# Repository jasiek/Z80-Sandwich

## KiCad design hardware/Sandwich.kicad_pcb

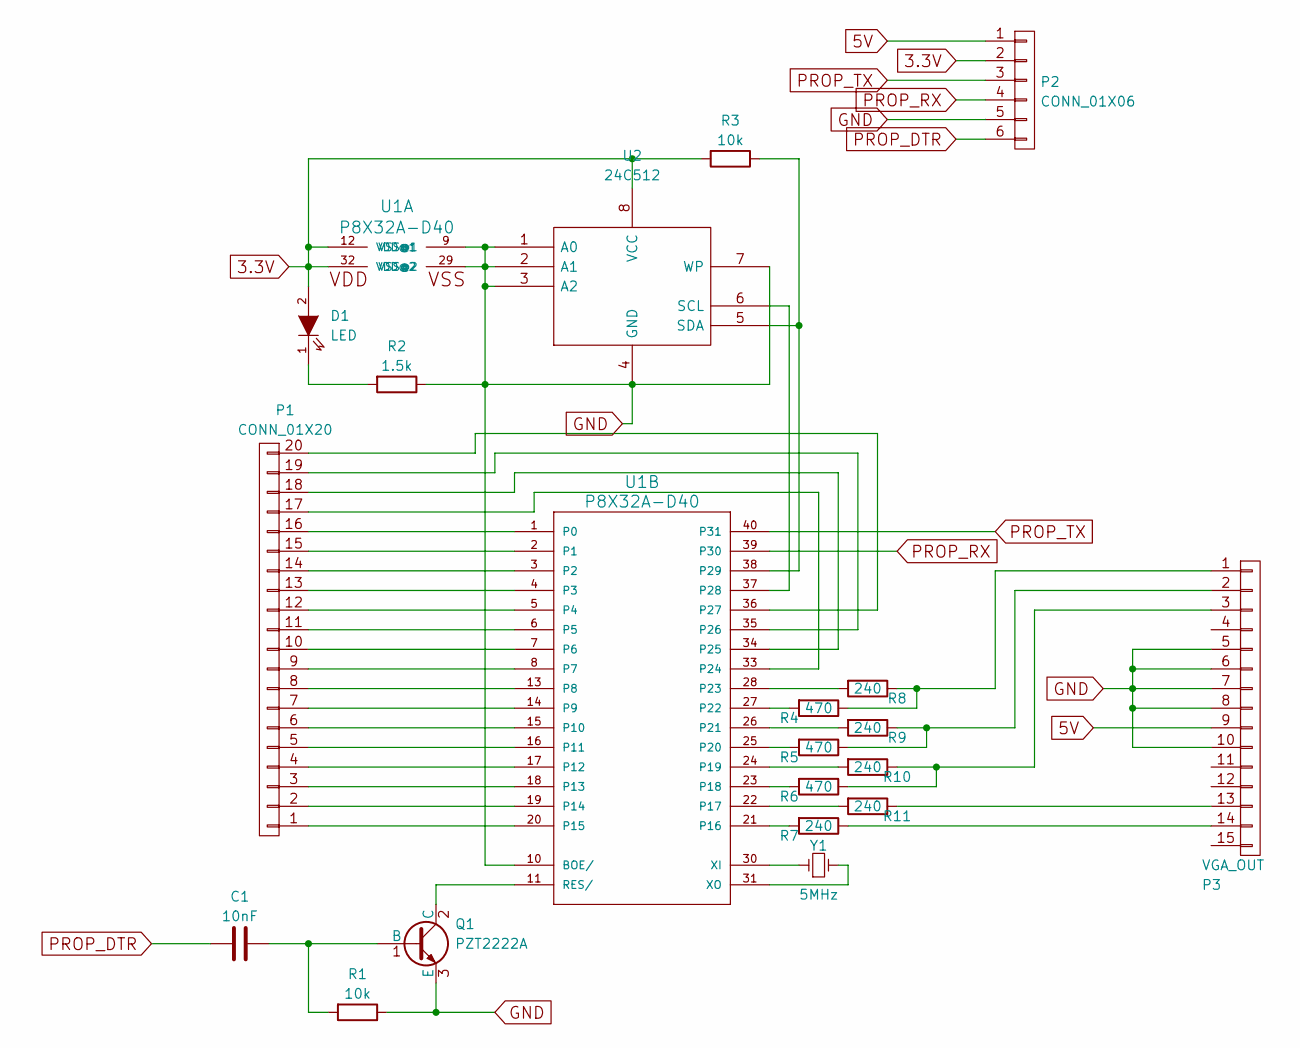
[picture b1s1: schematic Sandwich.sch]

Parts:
C1: 10nF; C_Disc_D3_P2.5
D1: LED; LED-5MM
P1: CONN_01X20; Pin_Header_Straight_1x20
P2: CONN_01X06; Pin_Header_Straight_1x06
P3: VGA_OUT; conn_SPC15430
Q1: PZT2222A; SOT-223
R1, R3: 10k; Resistor_Horizontal_RM10mm
R2: 1.5k; Resistor_Horizontal_RM10mm
R4, R5, R6: 470; Resistor_Horizontal_RM10mm
R7, R8, R9, R10, R11: 240; Resistor_Horizontal_RM10mm
U1: P8X32A-D40; DIP-40_W15.24mm_LongPads
U2: 24C512; DIP-8_W7.62mm_LongPads
Y1: 5MHz; Crystal_HC49-U_Vertical

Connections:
3.3V: D1.2 (A), P2.2, R3.2, U1.12 (VDD@1), U1.32 (VDD@2), U2.8 (VCC); also elsewhere on the board
5V: P2.1, P3.9
GND: P2.5, P3.5, P3.6, P3.7, P3.8, P3.10, Q1.3 (E), R1.1, R2.1, U1.9 (VSS@1), U1.10 (BOE/), U1.29 (VSS@2), U2.1 (A0), U2.2 (A1), U2.3 (A2), U2.4 (GND), U2.7 (WP); also elsewhere on the board
unnamed: C1.1, Q1.1 (B), R1.2
unnamed: D1.1 (K), R2.2
unnamed: P1.1, U1.20 (P15)
unnamed: P1.2, U1.19 (P14)
unnamed: P1.3, U1.18 (P13)
unnamed: P1.4, U1.17 (P12)
unnamed: P1.5, U1.16 (P11)
unnamed: P1.6, U1.15 (P10)
unnamed: P1.7, U1.14 (P9)
unnamed: P1.8, U1.13 (P8)
unnamed: P1.9, U1.8 (P7)
unnamed: P1.10, U1.7 (P6)
unnamed: P1.11, U1.6 (P5)
unnamed: P1.12, U1.5 (P4)
unnamed: P1.13, U1.4 (P3)
unnamed: P1.14, U1.3 (P2)
unnamed: P1.15, U1.2 (P1)
unnamed: P1.16, U1.1 (P0)
unnamed: P1.17, U1.33 (P24)
unnamed: P1.18, U1.34 (P25)
unnamed: P1.19, U1.35 (P26)
unnamed: P1.20, U1.36 (P27)
unnamed: P3.1, R4.1, R8.1
unnamed: P3.2, R5.1, R9.1
unnamed: P3.3, R6.1, R10.1
unnamed: P3.13, R11.1
unnamed: P3.14, R7.1
unnamed: Q1.2 (C), U1.11 (RES/)
unnamed: R3.1, U1.38 (P29), U2.5 (SDA)
unnamed: R4.2, U1.27 (P22)
unnamed: R5.2, U1.25 (P20)
unnamed: R6.2, U1.23 (P18)
unnamed: R7.2, U1.21 (P16)
unnamed: R8.2, U1.28 (P23)
unnamed: R9.2, U1.26 (P21)
unnamed: R10.2, U1.24 (P19)
unnamed: R11.2, U1.22 (P17)
unnamed: U1.30 (XI), Y1.1
unnamed: U1.31 (XO), Y1.2
unnamed: U1.37 (P28), U2.6 (SCL)
PROP_DTR: C1.2, P2.6
PROP_RX: P2.4, U1.39 (P30)
PROP_TX: P2.3, U1.40 (P31)

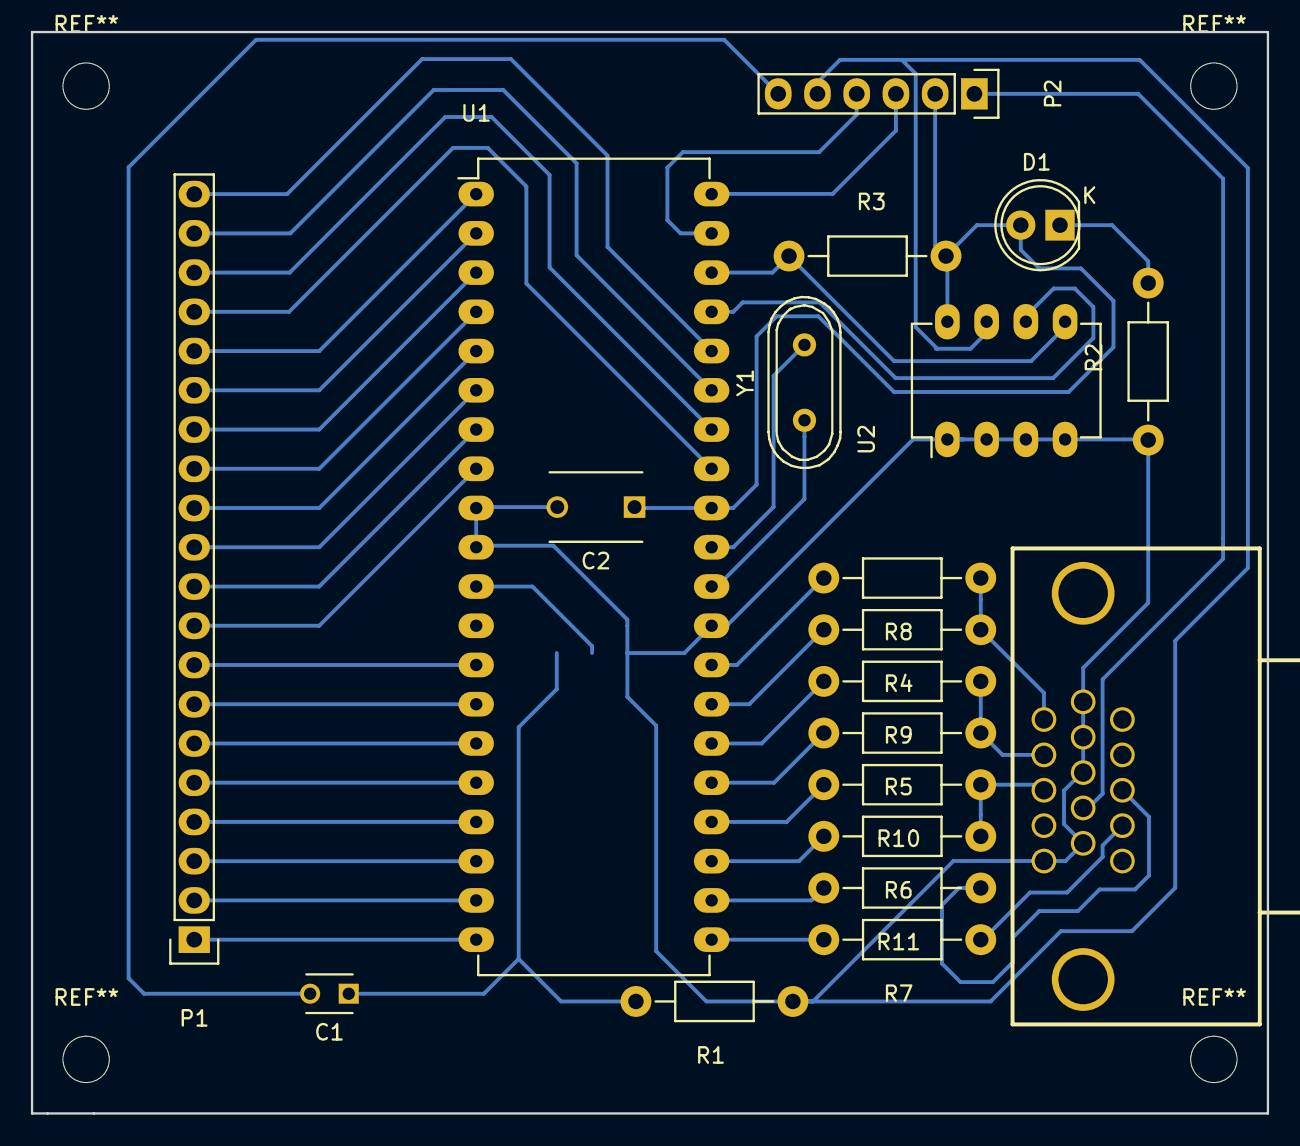
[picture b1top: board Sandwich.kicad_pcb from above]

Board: 2 copper layers, 80.0 x 70.0 mm, 21 parts (1 on the bottom side), 46 nets.

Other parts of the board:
C2: 100nF; C_Disc_D6_P5

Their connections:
3.3V: C2.1; also elsewhere on the board
GND: C2.2; also elsewhere on the board

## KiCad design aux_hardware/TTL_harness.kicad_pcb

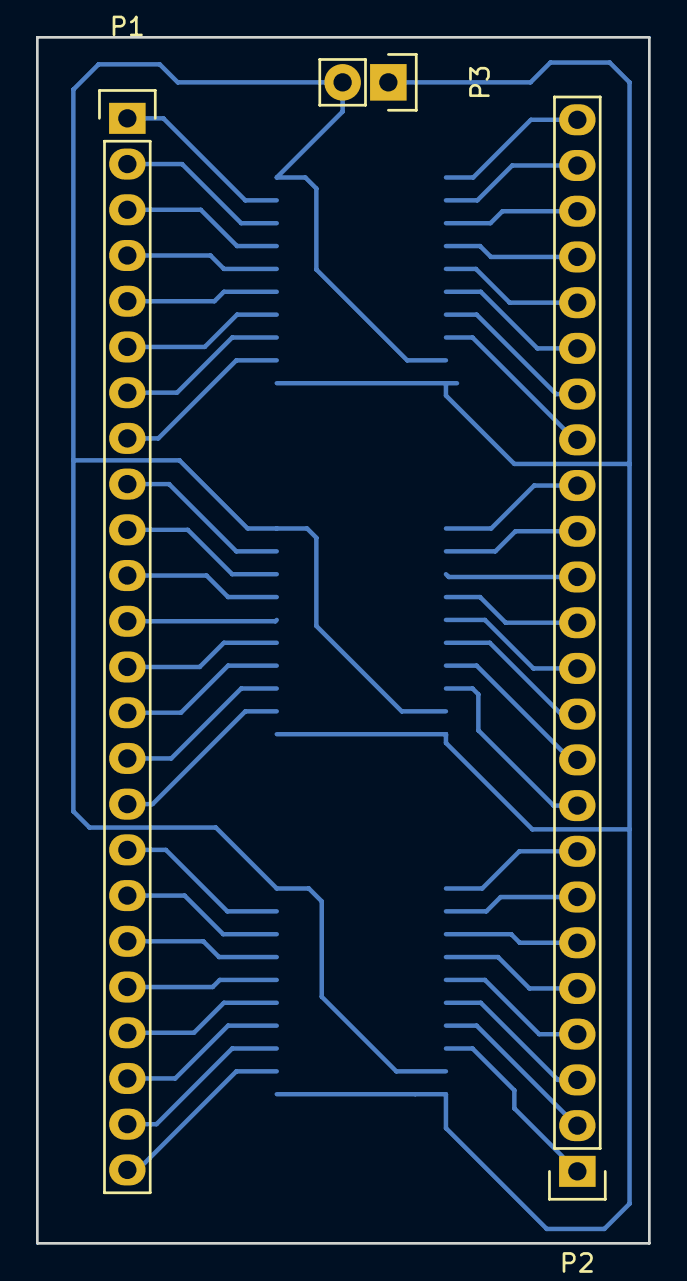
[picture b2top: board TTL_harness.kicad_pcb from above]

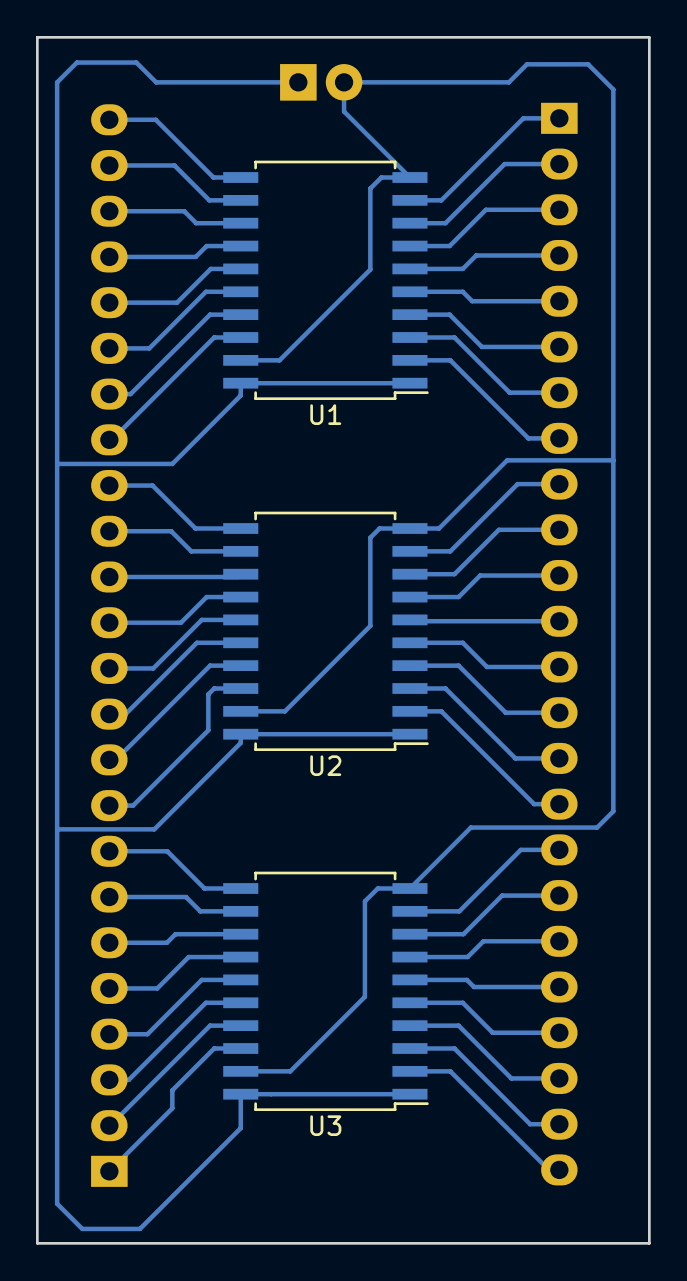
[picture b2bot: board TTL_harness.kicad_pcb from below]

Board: 2 copper layers, 34.0 x 67.0 mm, 6 parts (3 on the bottom side), 50 nets.

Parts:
P1, P2: CONN_01X24; Pin_Header_Straight_1x24
P3: CONN_01X02; Pin_Header_Straight_1x02
U1, U2, U3: 74LVC245; SOIC-20_7.5x12.8mm_Pitch1.27mm

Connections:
GND: P3.2, U1.10, U1.19, U2.10, U2.19, U3.10, U3.19
unnamed: P1.1, U1.9
unnamed: P1.2, U1.8
unnamed: P1.3, U1.7
unnamed: P1.4, U1.6
unnamed: P1.5, U1.5
unnamed: P1.6, U1.4
unnamed: P1.7, U1.3
unnamed: P1.8, U1.2
unnamed: P1.9, U2.9
unnamed: P1.10, U2.8
unnamed: P1.11, U2.7
unnamed: P1.12, U2.6
unnamed: P1.13, U2.5
unnamed: P1.14, U2.4
unnamed: P1.15, U2.3
unnamed: P1.16, U2.2
unnamed: P1.17, U3.9
unnamed: P1.18, U3.8
unnamed: P1.19, U3.7
unnamed: P1.20, U3.6
unnamed: P1.21, U3.5
unnamed: P1.22, U3.4
unnamed: P1.23, U3.3
unnamed: P1.24, U3.2
unnamed: P2.1, U3.18
unnamed: P2.2, U3.17
unnamed: P2.3, U3.16
unnamed: P2.4, U3.15
unnamed: P2.5, U3.14
unnamed: P2.6, U3.13
unnamed: P2.7, U3.12
unnamed: P2.8, U3.11
unnamed: P2.9, U2.18
unnamed: P2.10, U2.17
unnamed: P2.11, U2.16
unnamed: P2.12, U2.15
unnamed: P2.13, U2.14
unnamed: P2.14, U2.13
unnamed: P2.15, U2.12
unnamed: P2.16, U2.11
unnamed: P2.17, U1.18
unnamed: P2.18, U1.17
unnamed: P2.19, U1.16
unnamed: P2.20, U1.15
unnamed: P2.21, U1.14
unnamed: P2.22, U1.13
unnamed: P2.23, U1.12
unnamed: P2.24, U1.11
VCC: P3.1, U1.1, U1.20, U2.1, U2.20, U3.1, U3.20

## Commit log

2016-02-01 Generated project skeleton.
2016-02-01 CPU & voltage regulator.
2016-02-04 Added Parallax Propeller libraries.
2016-02-04 Started working on the VGA interface.
2016-02-07 Added a circuit for resetting the Propeller for programming when DTR gets activated.
2016-02-13 Updated schematics.
2016-02-15 Schematics WIP
2016-02-15 Updated schematics, PCB layout is nearly done.
2016-02-16 Production ready VGA board.
2016-02-16 .gitignore
2016-02-17 Test harness.
2016-02-18 Removed fill area.
2016-02-19 Regenerated both PCBs
2016-02-20 Mounting holes and drill files.
2016-02-23 TX/RX pins were switched over. Regenerated PCB and everything else.
2016-02-27 Added a cap.
2016-02-27 Initial stab at VGA display.
2016-02-27 Added .gitignore for propeller projects.
